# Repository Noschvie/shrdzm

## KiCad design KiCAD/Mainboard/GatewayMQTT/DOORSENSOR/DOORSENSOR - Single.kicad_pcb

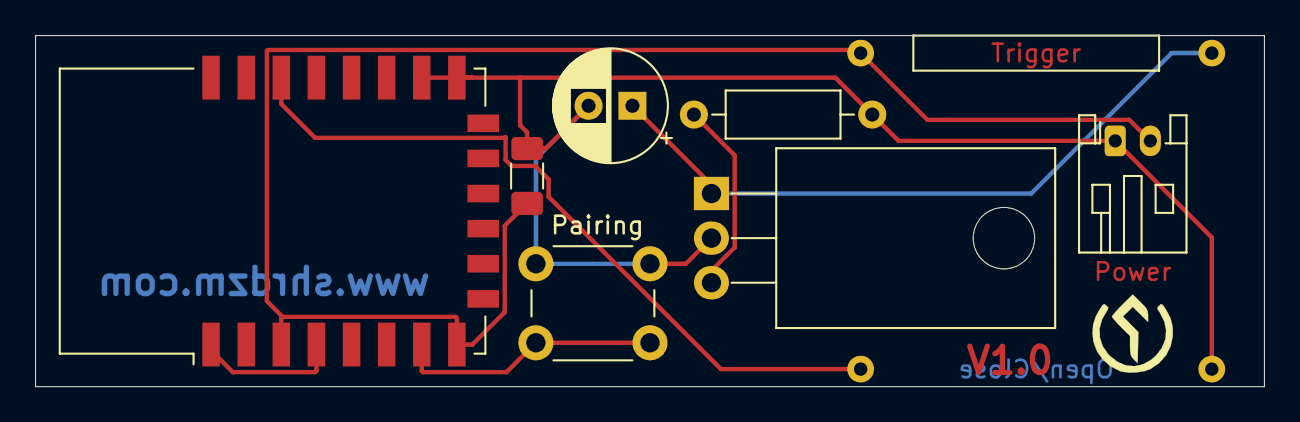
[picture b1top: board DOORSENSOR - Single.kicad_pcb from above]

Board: 2 copper layers, 70.0 x 20.0 mm, 9 parts (1 on the bottom side), 7 nets.

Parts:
C1: CP; CP_Radial_D6.3mm_P2.50mm
C2: C; C_1206_3216Metric_Pad1.33x1.80mm_HandSolder
J4: Power; JST_PH_S2B-PH-K_1x02_P2.00mm_Horizontal
Q1: IRLZ44N; TO-220-3_Horizontal_TabDown
R1: R; R_Axial_DIN0207_L6.3mm_D2.5mm_P10.16mm_Horizontal
SW1: Trigger; Magnetic Reed Relay
SW2: Pairing; SW_PUSH_6mm
SW3: Open/Close; Magnetic Reed Relay
U1: ESP-12F; ESP-12E

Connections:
+3V3: C2.2, J4.2, SW1.1, U1.3, U1.8
GND: C1.2, C2.1, J4.1, Q1.2, R1.2, SW2.2, SW3.2, U1.15, U1.16
unnamed: C1.1, Q1.1, SW1.2
unnamed: Q1.3, R1.1
unnamed: SW2.1, U1.7
unnamed: SW3.1, U1.20
unnamed: U1.1, U1.4

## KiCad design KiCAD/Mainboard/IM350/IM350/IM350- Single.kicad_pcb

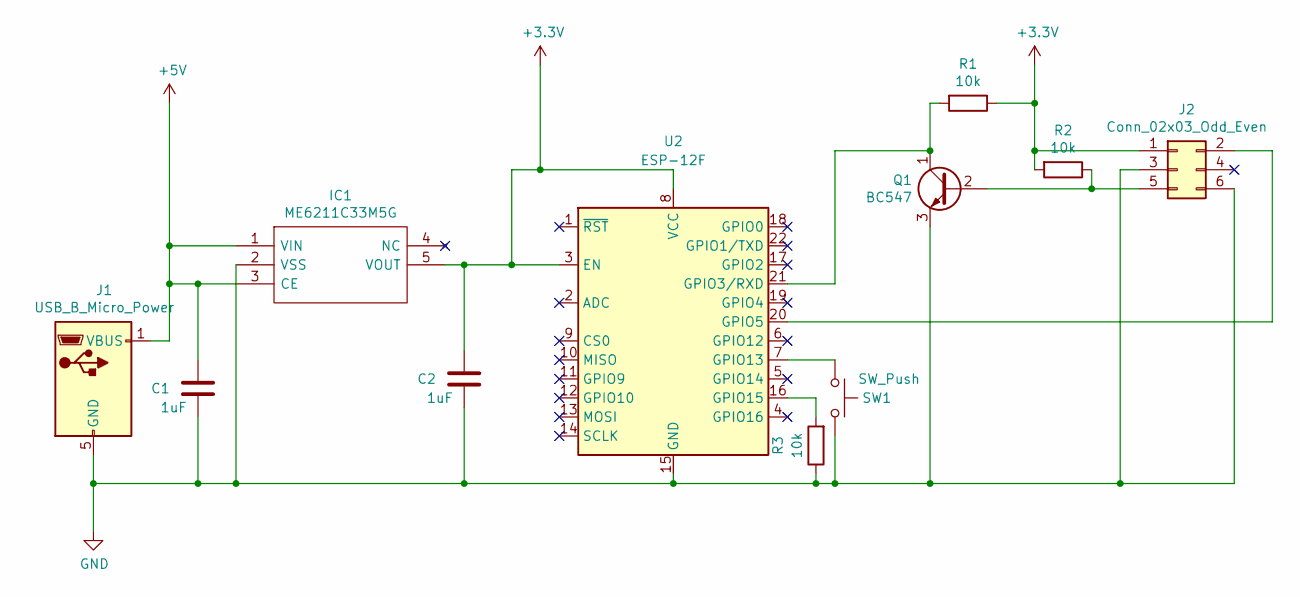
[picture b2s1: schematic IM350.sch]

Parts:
C1, C2: 1uF; C_0805_2012Metric_Pad1.18x1.45mm_HandSolder
IC1: ME6211C33M5G; SOT95P282X145-5N; Manufacturer_Part_Number ME6211C33M5G
J1: USB_B_Micro_Power; USB_Micro-B_Power
J2: Conn_02x03_Odd_Even; PinHeader_2x03_P2.54mm_Vertical
Q1: BC547; TO-92_Inline_Horizontal1
R1, R2, R3: 10k; R_0805_2012Metric_Pad1.20x1.40mm_HandSolder
SW1: SW_Push; SW_PUSH_6mm
U2: ESP-12F; ESP-12E

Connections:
+3V3: C2.1, IC1.5 (VOUT), J2.1, R1.1, R2.2, U2.3 (EN), U2.8 (VCC)
+5V: C1.1, IC1.1 (VIN), IC1.3 (CE), J1.1 (VBUS)
GND: C1.2, C2.2, IC1.2 (VSS), J1.5 (GND), J2.3, J2.6, Q1.3 (E), R3.1, SW1.2, U2.15 (GND)
unnamed: J2.2, U2.20 (GPIO5)
unnamed: J2.5, Q1.2 (B), R2.1
unnamed: Q1.1 (C), R1.2, U2.21 (GPIO3/RXD)
unnamed: R3.2, U2.16 (GPIO15)
unnamed: SW1.1, U2.7 (GPIO13)

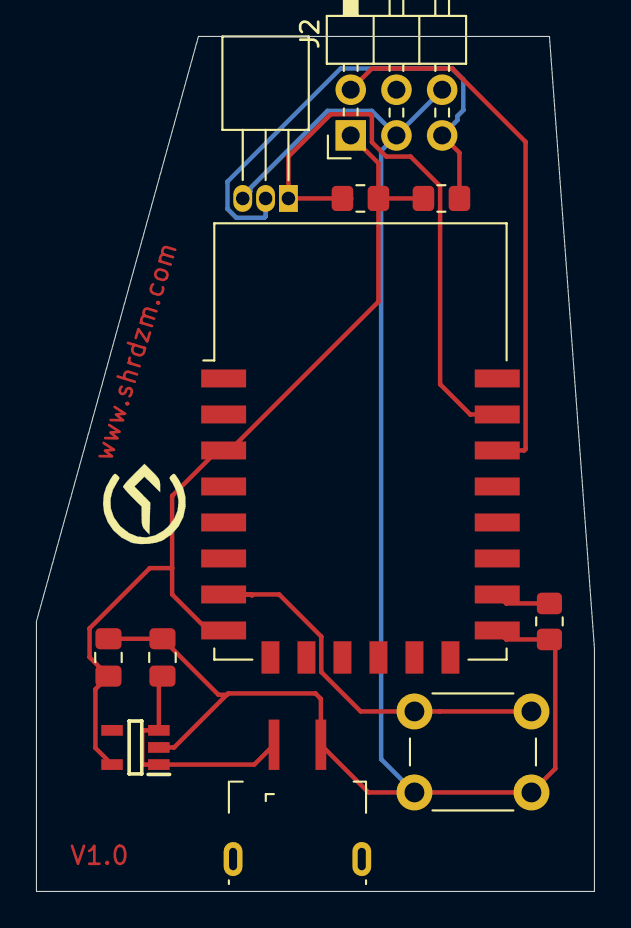
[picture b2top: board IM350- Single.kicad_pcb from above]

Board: 2 copper layers, 31.0 x 47.5 mm, 11 parts (0 on the bottom side), 8 nets.

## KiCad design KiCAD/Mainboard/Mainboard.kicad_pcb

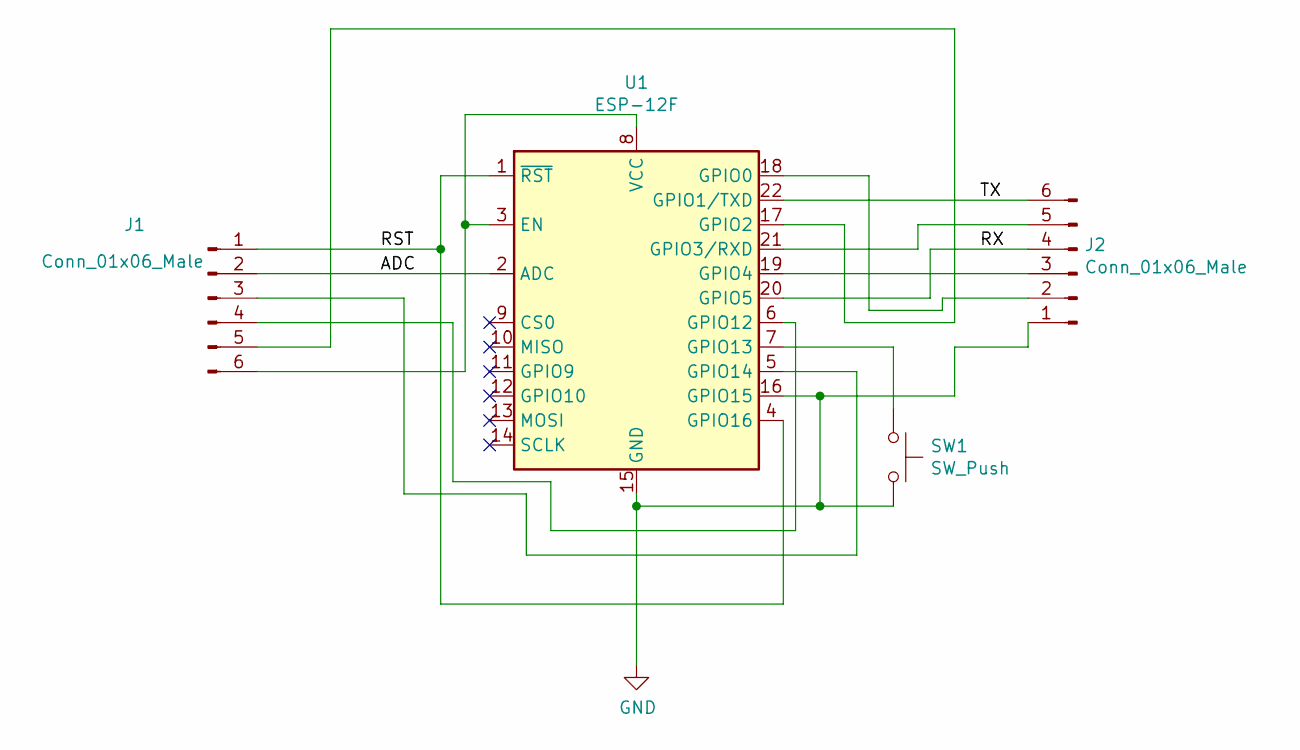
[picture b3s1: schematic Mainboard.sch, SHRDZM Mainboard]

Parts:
J1, J2: Conn_01x06_Male; PinHeader_1x06_P2.54mm_Vertical
SW1: SW_Push; SW_SPST_CK_RS282G05A3
U1: ESP-12F; ESP-12E

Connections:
/ADC: J1.2, U1.2 (ADC)
/RST: J1.1, U1.1 (~RST), U1.4 (GPIO16)
/RX: J2.4, U1.20 (GPIO5)
/TX: J2.6, U1.22 (GPIO1/TXD)
GND: J2.1, SW1.2, U1.15 (GND), U1.16 (GPIO15)
unnamed: J1.3, U1.5 (GPIO14)
unnamed: J1.4, U1.6 (GPIO12)
unnamed: J1.5, U1.17 (GPIO2)
unnamed: J1.6, U1.3 (EN), U1.8 (VCC)
unnamed: J2.2, U1.18 (GPIO0)
unnamed: J2.3, U1.19 (GPIO4)
unnamed: J2.5, U1.21 (GPIO3/RXD)
unnamed: SW1.1, U1.7 (GPIO13)

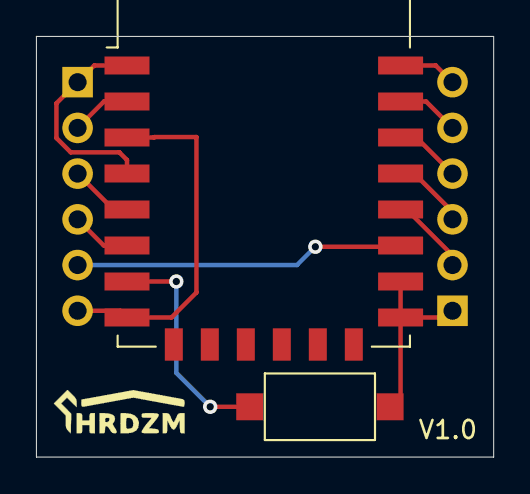
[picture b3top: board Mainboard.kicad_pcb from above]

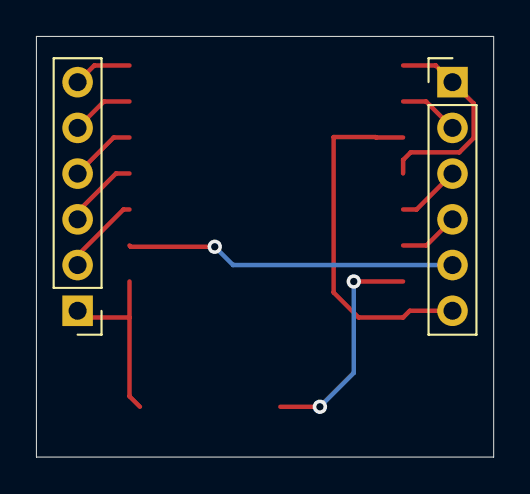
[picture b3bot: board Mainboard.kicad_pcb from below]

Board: 2 copper layers, 25.4 x 23.4 mm, 4 parts (2 on the bottom side), 13 nets.

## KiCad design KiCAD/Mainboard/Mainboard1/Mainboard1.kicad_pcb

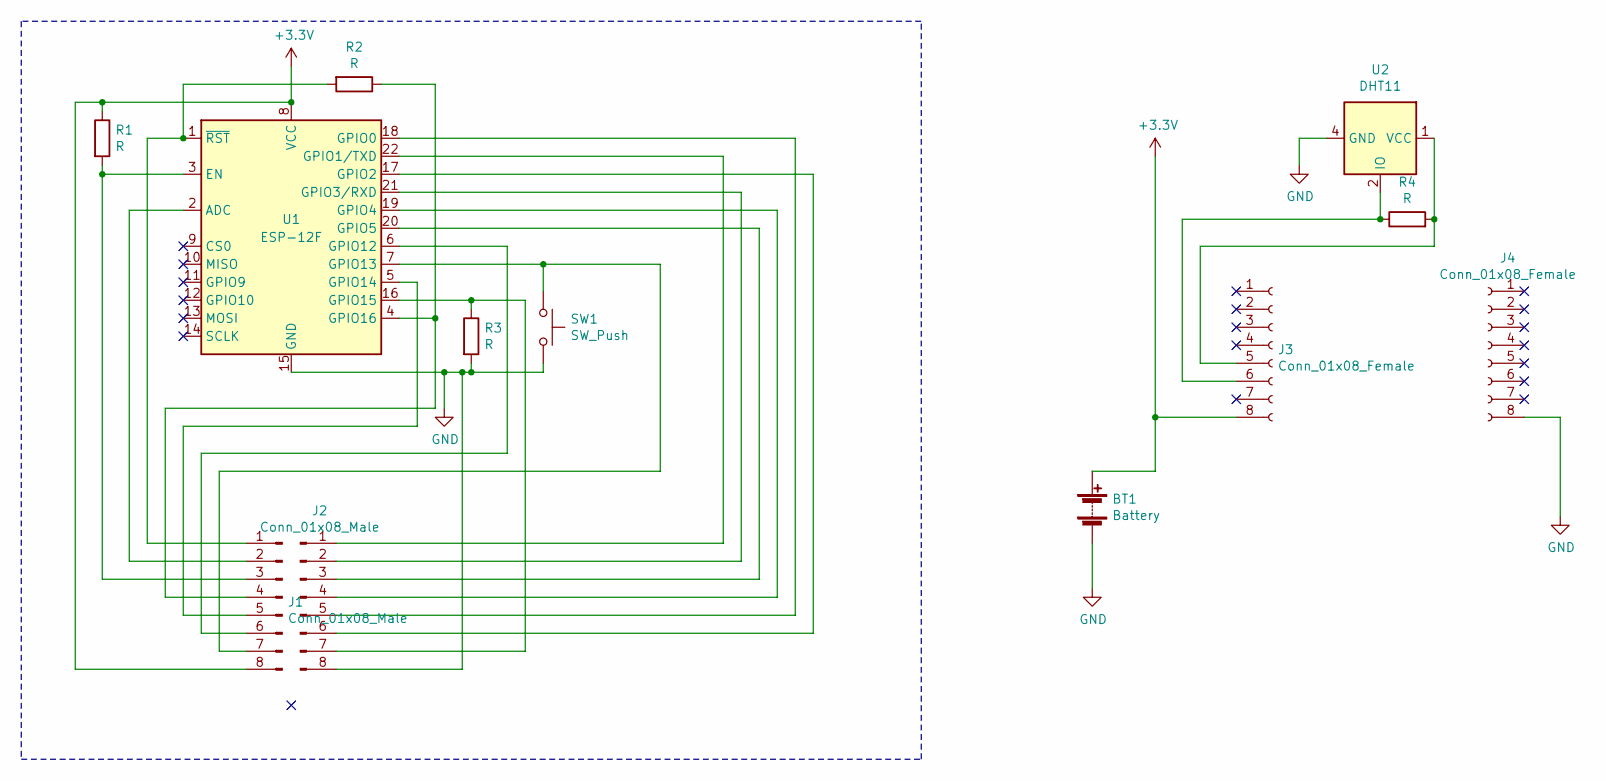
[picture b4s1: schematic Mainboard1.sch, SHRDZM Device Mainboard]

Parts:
BT1: Battery
J1, J2: Conn_01x08_Male; PinHeader_1x08_P2.54mm_Vertical
J3, J4: Conn_01x08_Female; PinSocket_1x08_P2.54mm_Vertical
R1, R2, R3: R; R_0603_1608Metric_Pad0.98x0.95mm_HandSolder
R4: R; R_Axial_DIN0207_L6.3mm_D2.5mm_P10.16mm_Horizontal
SW1: SW_Push; SW_SPST_CK_RS282G05A3
U1: ESP-12F; ESP-12E
U2: DHT11; Aosong_DHT11_5.5x12.0_P2.54mm

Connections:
+3V3: BT1.1 (+), J1.8, J3.8, R1.1, U1.8 (VCC)
GND: BT1.2 (-), J2.8, J4.8, R3.2, SW1.2, U1.15 (GND), U2.4 (GND)
unnamed: J1.1, R2.2, U1.1 (~RST)
unnamed: J1.2, U1.2 (ADC)
unnamed: J1.3, R1.2, U1.3 (EN)
unnamed: J1.4, R2.1, U1.4 (GPIO16)
unnamed: J1.5, U1.5 (GPIO14)
unnamed: J1.6, U1.6 (GPIO12)
unnamed: J1.7, SW1.1, U1.7 (GPIO13)
unnamed: J2.1, U1.22 (GPIO1/TXD)
unnamed: J2.2, U1.21 (GPIO3/RXD)
unnamed: J2.3, U1.20 (GPIO5)
unnamed: J2.4, U1.19 (GPIO4)
unnamed: J2.5, U1.18 (GPIO0)
unnamed: J2.6, U1.17 (GPIO2)
unnamed: J2.7, R3.1, U1.16 (GPIO15)
unnamed: J3.5, R4.2, U2.1 (VCC)
unnamed: J3.6, R4.1, U2.2 (IO)

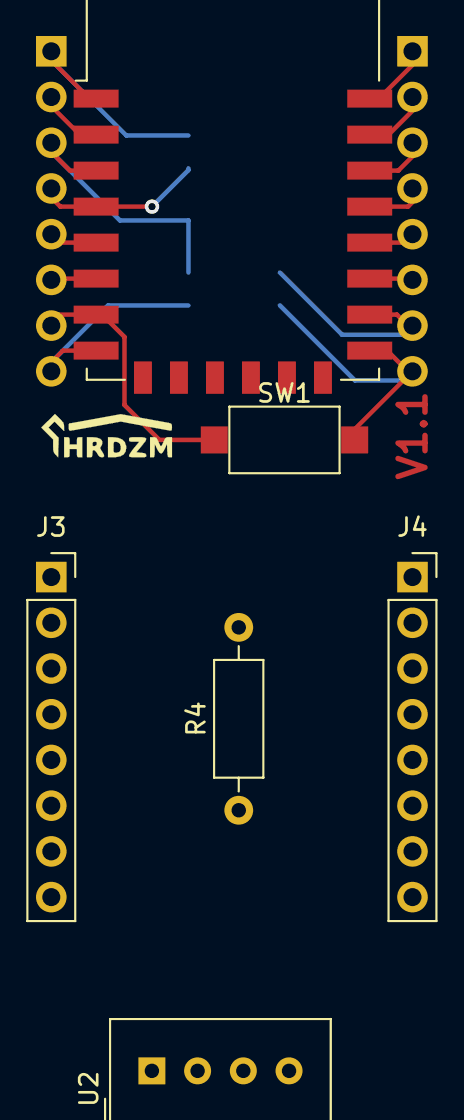
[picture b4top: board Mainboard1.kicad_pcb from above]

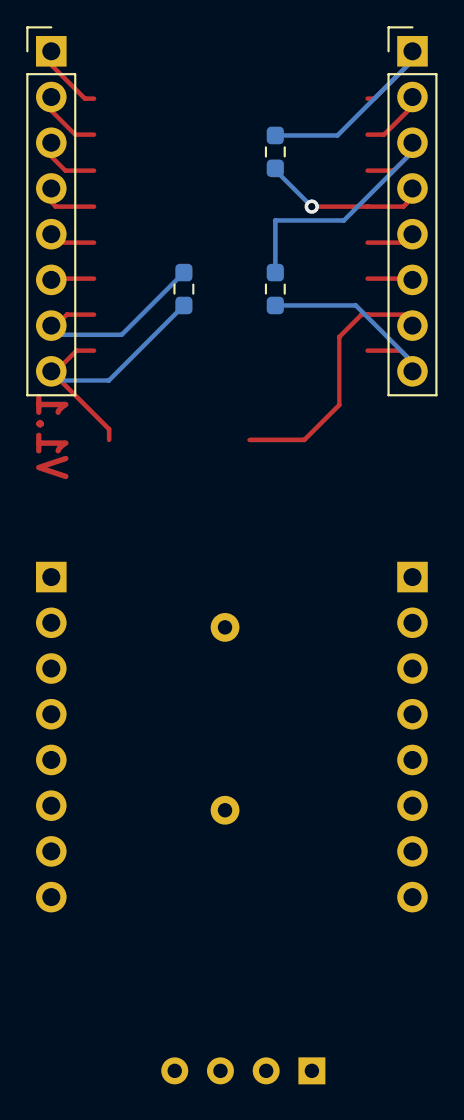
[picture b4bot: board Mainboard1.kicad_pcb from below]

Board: 2 copper layers, 11 parts (5 on the bottom side), 18 nets.

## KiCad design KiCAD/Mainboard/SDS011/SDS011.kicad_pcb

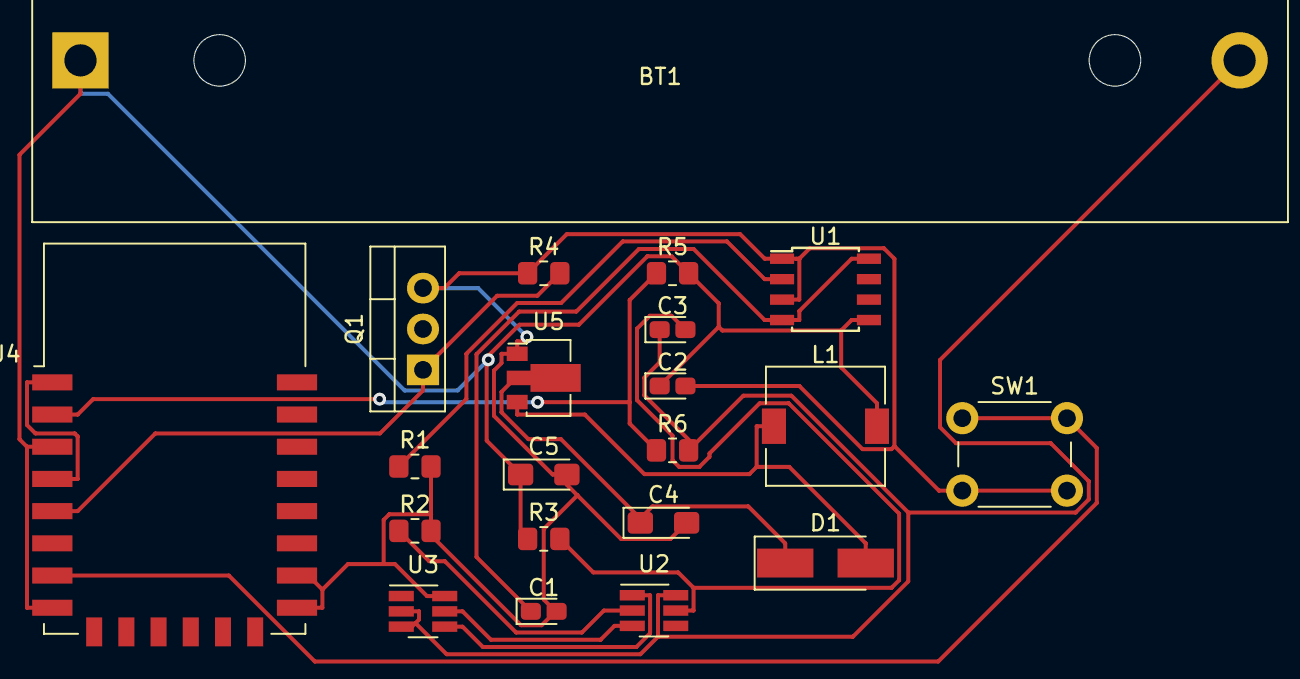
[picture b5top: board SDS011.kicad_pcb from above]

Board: 2 copper layers, 21 parts (0 on the bottom side), 15 nets.

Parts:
BT1: Battery_Cell; BatteryHolder_MPD_BH-18650-PC2
C1, C3: 0.1uF; CP_EIA-1608-10_AVX-L_Pad1.25x1.05mm_HandSolder
C2: 10uF; CP_EIA-1608-10_AVX-L_Pad1.25x1.05mm_HandSolder
C4: 22uF; CP_EIA-3216-18_Kemet-A_Pad1.58x1.35mm_HandSolder
C5: 47uF; CP_EIA-3216-18_Kemet-A_Pad1.58x1.35mm_HandSolder
D1: D_Schottky; D_SMA_Handsoldering
L1: 100uH; L_7.3x7.3_H4.5
Q1: IRLZ44N; TO-220-3_Vertical
R1, R4: 10k; R_0805_2012Metric_Pad1.20x1.40mm_HandSolder
R2: 1k; R_0805_2012Metric_Pad1.20x1.40mm_HandSolder
R3: 100; R_0805_2012Metric_Pad1.20x1.40mm_HandSolder
R5: 330k; R_0805_2012Metric_Pad1.20x1.40mm_HandSolder
R6: 100k; R_0805_2012Metric_Pad1.20x1.40mm_HandSolder
SW1: Pairing; SW_PUSH_6mm
U1: TP4056; TP4056_SOP-8-PP
U2: DW01; SOT-23-6_Handsoldering
U3: FS8205A; SOT-23-6_Handsoldering
U4: ESP-12F; ESP-12E
U5: HT7750-1-SOT89; SOT-89-3

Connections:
unnamed: BT1.1, C2.1, C5.1, L1.2, R3.1, R5.2, U1.5, U4.3, U4.8
unnamed: BT1.2, C3.1, R6.2, U2.6, U3.2, U3.3
unnamed: C1.1, U1.4, U1.8
unnamed: C1.2, C2.2, C4.2, C5.2, Q1.3, R1.2, R2.2, R4.1, SW1.2, U1.1, U1.3, U3.6, U4.15, U4.16, U5.1
unnamed: C3.2, R3.2, U2.5
unnamed: C4.1, D1.1, U5.2
unnamed: D1.2, L1.1, U5.3
unnamed: Q1.1, R4.2, U4.5
unnamed: R1.1, U1.2
unnamed: R2.1, U2.2
unnamed: R5.1, R6.1, U4.2
unnamed: SW1.1, U4.7
unnamed: U2.1, U3.4
unnamed: U2.3, U3.5
unnamed: U4.1, U4.4
